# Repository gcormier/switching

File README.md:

# Switching Regulator
Simple PCB to design and fab a switching regulator for 24VAC to 3.3VDC. Various test points for bench testing and load testing.

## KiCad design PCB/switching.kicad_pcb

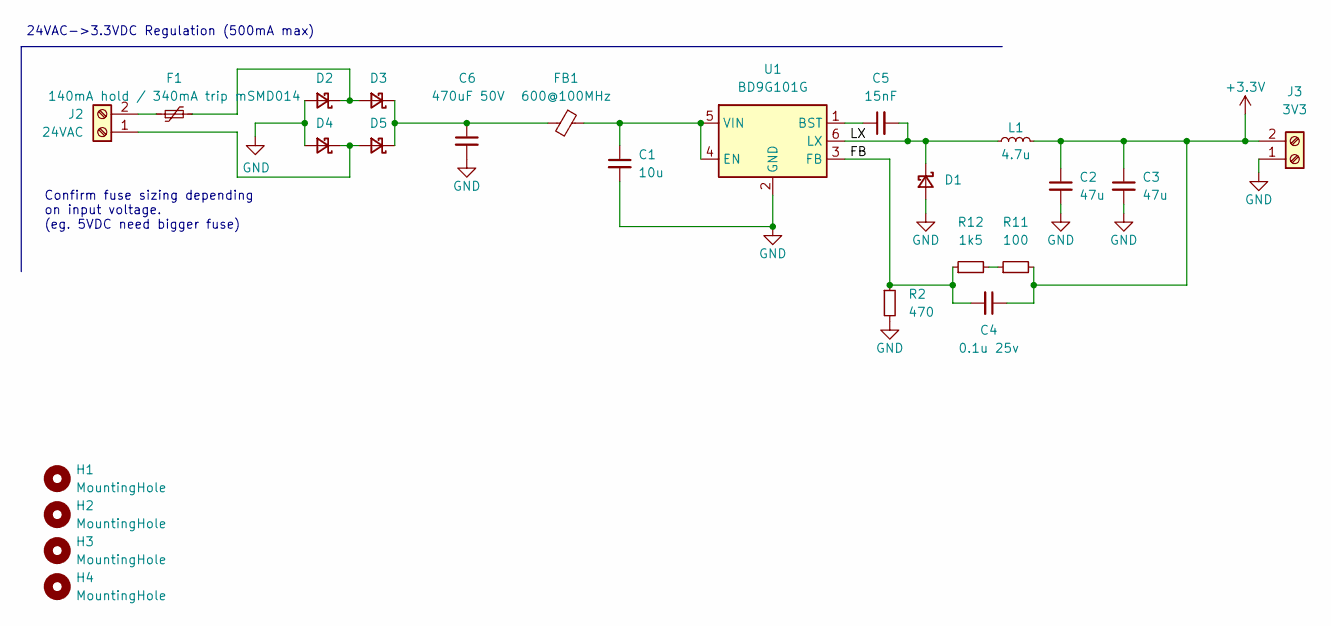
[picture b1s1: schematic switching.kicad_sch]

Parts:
C1: 10u; C_1206_3216Metric; LCSC C13585
C2, C3: 47u; C_1206_3216Metric; LCSC C96123
C4: 0.1u 25v; C_0603_1608Metric; LCSC C14663
C5: 15nF; C_0603_1608Metric; LCSC C1596
C6: 470uF 50V; CP_Elec_10x10; LCSC C125977
D1, D2, D3, D4, D5: SS210; D_SMA; LCSC C14996
F1: 140mA hold / 340mA trip mSMD014; Fuse_1812_4532Metric; LCSC C70106
FB1: 600@100MHz; L_0805_2012Metric; LCSC C1017
H1, H2, H3, H4: MountingHole; MountingHole_3.2mm_M3
J2: 24VAC; TerminalBlock_Phoenix_MKDS-1,5-2-5.08_1x02_P5.08mm_Horizont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; Part 1935161; LCSC a
J3: 3V3; TerminalBlock_Phoenix_MKDS-1,5-2-5.08_1x02_P5.08mm_Horizont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; Part 1935161; LCSC a
L1: 4.7u; L_Sunlord_MWSA0402_4.4x4.2mm; LCSC C408337
R2: 470; R_0402_1005Metric; LCSC C25117
R11: 100; R_0402_1005Metric; LCSC C25076
R12: 1k5; R_0402_1005Metric; LCSC C25867
U1: BD9G101G; SOT-23-6; LCSC C108761

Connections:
+3.3V: C2.1, C3.1, C4.1, J3.2, L1.2, R11.2
/FB: C4.2, R2.1, R12.1, U1.3 (FB)
/LX: C5.2, D1.1 (K), L1.1, U1.6 (LX)
GND: C1.2, C2.2, C3.2, C6.2, D1.2 (A), D2.2 (A), D4.2 (A), J3.1, R2.2, U1.2 (GND)
unnamed: C1.1, FB1.1, U1.4 (EN), U1.5 (VIN)
unnamed: C5.1, U1.1 (BST)
unnamed: C6.1, D3.1 (K), D5.1 (K), FB1.2
unnamed: D2.1 (K), D3.2 (A), F1.2
unnamed: D4.1 (K), D5.2 (A), J2.1
unnamed: F1.1, J2.2
unnamed: R11.1, R12.2

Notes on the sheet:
24VAC->3.3VDC Regulation (500mA max)
Confirm fuse sizing depending on input voltage. (eg. 5VDC need bigger fuse)

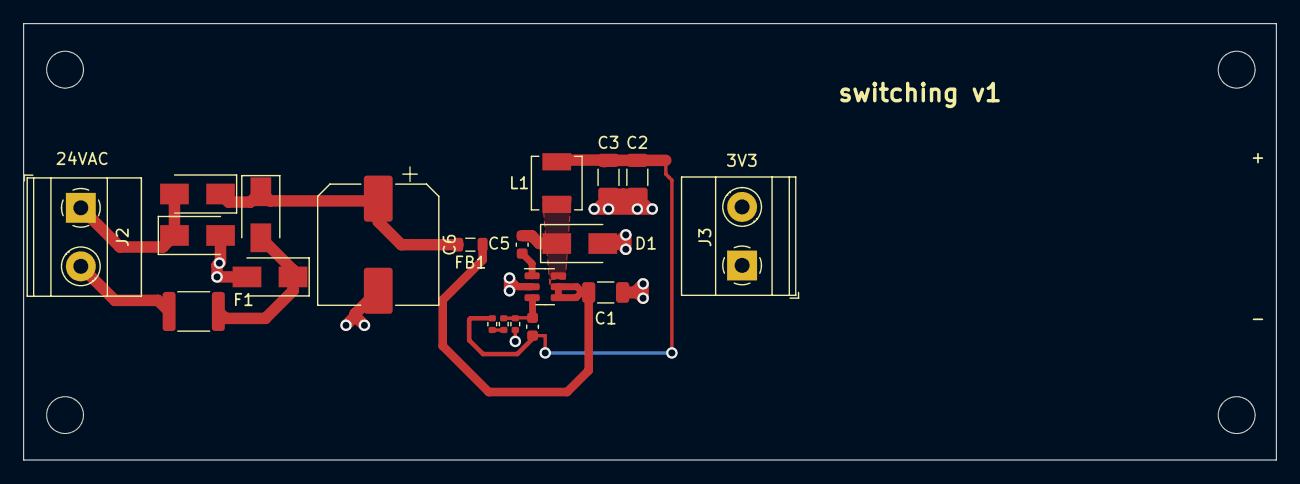
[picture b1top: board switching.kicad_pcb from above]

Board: 2 copper layers, 108.8 x 37.9 mm, 24 parts (0 on the bottom side), 11 nets.

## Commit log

2022-09-24 ignore backups
2022-09-24 ignore more
2022-09-24 ignore
2022-09-24 try ignore
2022-09-24 readme
2022-09-24 badhe
2022-09-24 change barrier diode
2022-09-24 silkscreen changes for v1
2022-09-24 actions update
2022-09-24 move silkscreen trigger build
2022-09-24 temp comment
2022-09-24 trigger again?
2022-09-24 4 layer
2022-09-24 convert to 2 layer
2022-09-24 add ground testpoints
2022-09-24 JLCJLCJLCJLC
2022-09-24 silkscreen update for polarity
2022-09-24 gerber filename
2022-10-08 smaller and smd only to use in designs
